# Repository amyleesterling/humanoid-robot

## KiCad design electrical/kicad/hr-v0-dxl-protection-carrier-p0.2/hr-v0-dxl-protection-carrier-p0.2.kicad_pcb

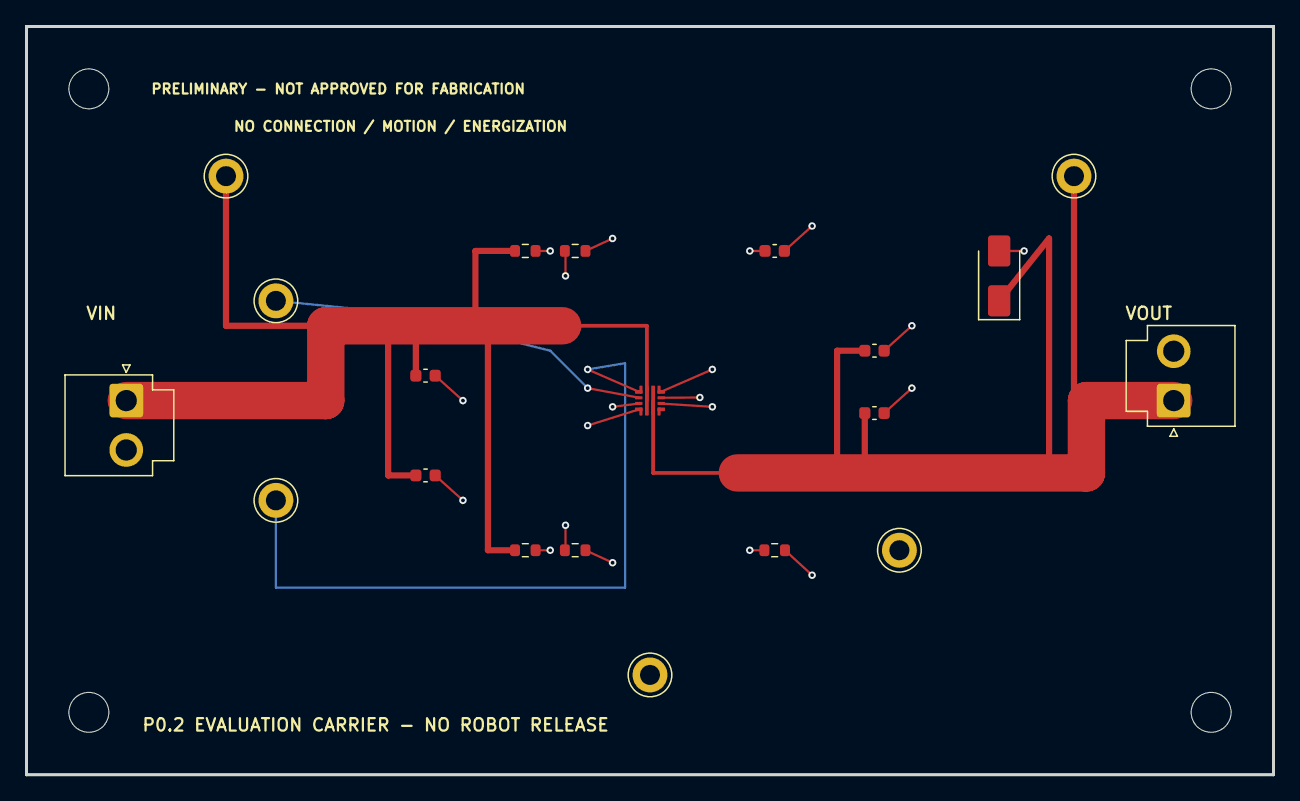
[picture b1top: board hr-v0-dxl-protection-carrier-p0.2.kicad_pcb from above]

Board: 4 copper layers, 100.0 x 60.0 mm, 24 parts (0 on the bottom side), 9 nets.

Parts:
CDV1: 2.2 nF C1608C0G1H222J080AA; C_0603_1608Metric
CINBULK1: 1 uF C1608X7R1V105K080AC; C_0603_1608Metric
CINHF1: 0.1 uF C1608X7R1H104K080AA; C_0603_1608Metric
COUTA1: 1 uF C1608X7R1V105K080AC; C_0603_1608Metric
COUTB1: 1 uF C1608X7R1V105K080AC; C_0603_1608Metric
DCLAMP1: B330A-13-F; D_SMA
JIN1: JST B2P-VH INPUT; JST_VH_B2P-VH_1x02_P3.96mm_Vertical
JOUT1: JST B2P-VH OUTPUT; JST_VH_B2P-VH_1x02_P3.96mm_Vertical
MH1, MH2, MH3, MH4: BOARD-ONLY M3; MOUNTING SELECTION REQUIRED; MountingHole_3.2mm_M3
RILM1: ASSEMBLY VARIANT: 1.65 k / 3.32 k; R_0603_1608Metric
ROVB1: 44.2 k RC0603FR-0744K2L; R_0603_1608Metric
ROVT1: 470 k RC0603FR-07470KL; R_0603_1608Metric
RUVB1: 49.9 k RC0603FR-0749K9L; R_0603_1608Metric
RUVT1: 365 k RC0603FR-07365KL; R_0603_1608Metric
TPFLT1: Keystone 5012 FLT; TestPoint_Keystone_5010-5014_Multipurpose
TPGND1: Keystone 5011 GND; TestPoint_Keystone_5010-5014_Multipurpose
TPILM1: Keystone 5012 ILM; TestPoint_Keystone_5010-5014_Multipurpose
TPOUT1: Keystone 5010 VOUT; TestPoint_Keystone_5010-5014_Multipurpose
TPSPLY1: Keystone 5012 SPLYGD; TestPoint_Keystone_5010-5014_Multipurpose
TPVIN1: Keystone 5010 VIN; TestPoint_Keystone_5010-5014_Multipurpose
U1: TPS259461LRPWR; TI_RPW0010A_HotRodQFN_2x2mm_P0.45mm_TI4225183A_P02

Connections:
ACT_0V_PE_BONDED: CDV1.2, CINBULK1.2, CINHF1.2, COUTA1.2, COUTB1.2, DCLAMP1.2, JIN1.2, JOUT1.2, RILM1.2, ROVB1.2, RUVB1.2, TPGND1.1, U1.8
BRANCH_FUSED_IN: CINBULK1.1, CINHF1.1, JIN1.1, ROVT1.1, RUVT1.1, TPVIN1.1, U1.5
BRANCH_LIMITED_OUT: COUTA1.1, COUTB1.1, DCLAMP1.1, JOUT1.1, TPOUT1.1, U1.6
DVDT_SET: CDV1.1, U1.7
FLT_DIAG: TPFLT1.1, U1.4
ILM_SET: RILM1.1, TPILM1.1, U1.9
OVLO_SET: ROVB1.1, ROVT1.2, U1.2
SPLYGD_DIAG: TPSPLY1.1, U1.3
UVLO_SET: RUVB1.1, RUVT1.2, U1.1

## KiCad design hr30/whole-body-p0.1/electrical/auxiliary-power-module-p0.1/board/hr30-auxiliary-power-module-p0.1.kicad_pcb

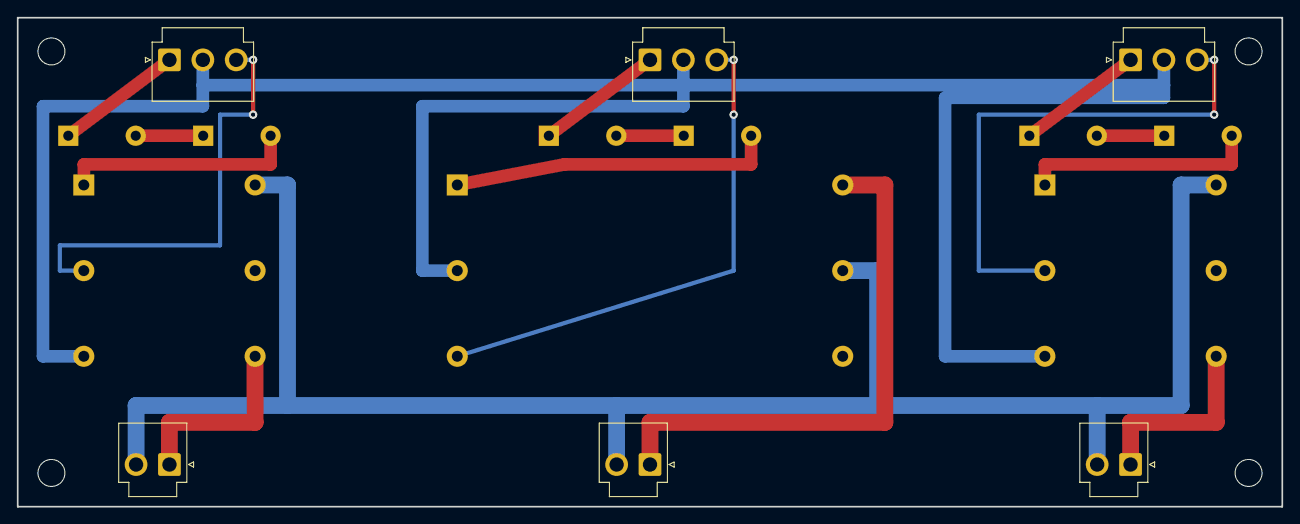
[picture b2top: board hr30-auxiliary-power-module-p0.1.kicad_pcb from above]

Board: 2 copper layers, 150.0 x 58.0 mm, 19 parts (0 on the bottom side), 17 nets.

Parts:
F1: COMPUTE input fuse - SELECTION REQUIRED; AUX_SELECTION_BLOCK
F2: HMI input fuse - SELECTION REQUIRED; AUX_SELECTION_BLOCK
F3: CONTROL input fuse - SELECTION REQUIRED; AUX_SELECTION_BLOCK
H1, H2, H3, H4: M3 BOARD MOUNT - STACK/FASTENER SELECTION REQUIRED; MountingHole_3.2mm_M3
JI1: COMPUTE 12 V input and active-low disable; JST_VH_B3P-VH-B_1x03_P3.96mm_Vertical
JI2: HMI 12 V input and active-low disable; JST_VH_B3P-VH-B_1x03_P3.96mm_Vertical
JI3: CONTROL 12 V input and active-low disable; JST_VH_B3P-VH-B_1x03_P3.96mm_Vertical
JO1: COMPUTE protected output; JST_VH_B2P-VH-B_1x02_P3.96mm_Vertical
JO2: HMI protected output; JST_VH_B2P-VH-B_1x02_P3.96mm_Vertical
JO3: CONTROL protected output; JST_VH_B2P-VH-B_1x02_P3.96mm_Vertical
RP1: COMPUTE reverse-polarity and inrush block - SELEC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; AUX_SELECTION_BLOCK
RP2: HMI reverse-polarity and inrush block - SELECTION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; AUX_SELECTION_BLOCK
RP3: CONTROL reverse-polarity and inrush block - SELEC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; AUX_SELECTION_BLOCK
U1: REC30E-2405SZ COMPUTE isolated converter; REC30E-Z
U2: TEN 40-1211E HMI isolated converter; TEN40E
U3: REC30E-2405SZ CONTROL isolated converter; REC30E-Z

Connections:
ACT_0V_CONTROLLED: JI1.2, JI2.2, JI3.2, U1.2, U2.2, U3.2
AUX_0V_STAR: JO1.2, JO2.2, JO3.2, U1.4, U2.5, U3.4
AUX_5V_SAFE: JO3.1, U3.6
COMPUTE_5V1: JO1.1, U1.6
COMPUTE_12V_FUSED: F1.2, RP1.1
COMPUTE_12V_PROTECTED: RP1.2, U1.1
COMPUTE_12V_RAW: F1.1, JI1.1
COMPUTE_DISABLE_N: JI1.3, U1.3
CONTROL_12V_FUSED: F3.2, RP3.1
CONTROL_12V_PROTECTED: RP3.2, U3.1
CONTROL_12V_RAW: F3.1, JI3.1
CONTROL_DISABLE_N: JI3.3, U3.3
HMI_5V0: JO2.1, U2.4
HMI_12V_FUSED: F2.2, RP2.1
HMI_12V_PROTECTED: RP2.2, U2.1
HMI_12V_RAW: F2.1, JI2.1
HMI_DISABLE_N: JI2.3, U2.3

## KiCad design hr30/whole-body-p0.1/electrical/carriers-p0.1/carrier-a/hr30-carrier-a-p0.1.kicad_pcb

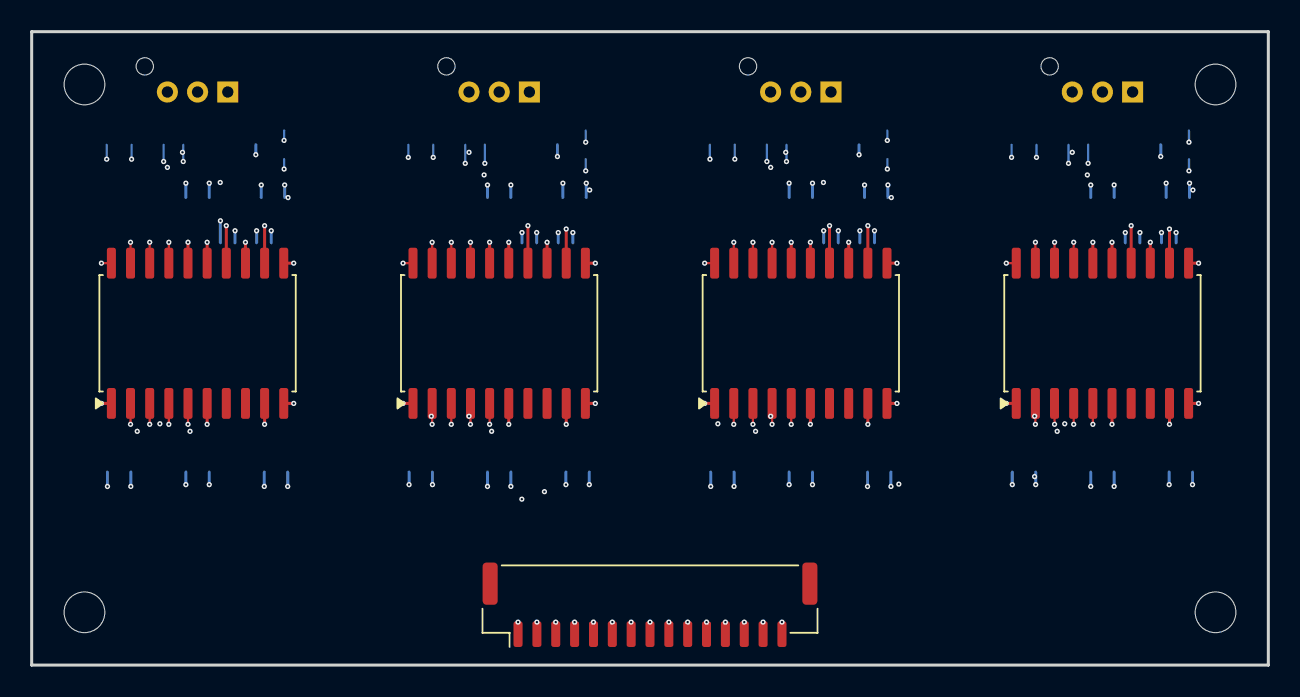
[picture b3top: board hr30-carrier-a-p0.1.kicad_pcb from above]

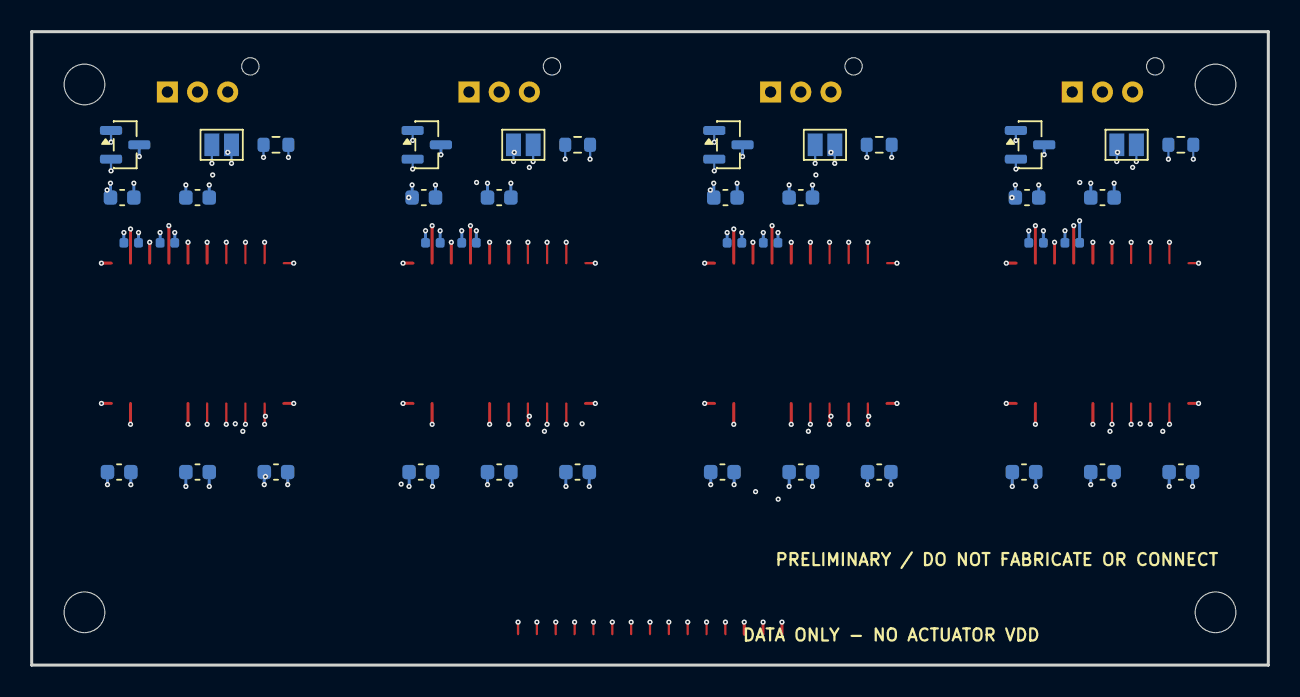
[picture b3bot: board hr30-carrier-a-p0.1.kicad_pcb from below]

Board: 6 copper layers, 82.0 x 42.0 mm, 53 parts (40 on the bottom side), 43 nets.

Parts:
C1A, C2A, C3A, C4A: 10nF 50V X7R; C_0603_1608Metric
C1B, C1D, C2B, C2D, C3B, C3D, C4B, C4D: 10uF 6.3V X5R; C_0603_1608Metric
C1C, C1E, C2C, C2E, C3C, C3E, C4C, C4E: 100nF 50V X7R; C_0603_1608Metric
D1RS, D2RS, D3RS, D4RS: SM712 RS-485 TVS; SOT-23
FB1N, FB2N, FB3N, FB4N: 330R@100MHz isolated return bead; L_0402_1005Metric
FB1P, FB2P, FB3P, FB4P: 330R@100MHz isolated supply bead; L_0402_1005Metric
J101: RS-LLEG data-only field; JST_PA_B03B-PASK-1
J102: RS-RLEG data-only field; JST_PA_B03B-PASK-1
J103: RS-LARM data-only field; JST_PA_B03B-PASK-1
J104: RS-RARM data-only field; JST_PA_B03B-PASK-1
JCA1: JST BM15B-GHS-TBT controller; JST_GH_BM15B-GHS-TBT_1x15-1MP_P1.25mm_Vertical
MHA1, MHA2, MHA3, MHA4: M2.5 BOARD-ONLY; TRAY STACK VALIDATION OPEN; MountingHole_2.7mm_M2.5
RT1, RT2, RT3, RT4: 120R 1% termination; R_0603_1608Metric
SJ1, SJ2, SJ3, SJ4: termination enable - OPEN; SolderJumper-2_P1.3mm_Open_Pad1.0x1.5mm
U101: ISOW1432DFMR RS-LLEG; SOIC-20W_7.5x12.8mm_P1.27mm
U102: ISOW1432DFMR RS-RLEG; SOIC-20W_7.5x12.8mm_P1.27mm
U103: ISOW1432DFMR RS-LARM; SOIC-20W_7.5x12.8mm_P1.27mm
U104: ISOW1432DFMR RS-RARM; SOIC-20W_7.5x12.8mm_P1.27mm

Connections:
CTRL_3V3: C1C.1, C2C.1, C3C.1, C4C.1, JCA1.3, U101.1, U102.1, U103.1, U104.1
CTRL_5V: C1A.1, C1B.1, C2A.1, C2B.1, C3A.1, C3B.1, C4A.1, C4B.1, JCA1.2, U101.9, U102.9, U103.9, U104.9
CTRL_GND: C1A.2, C1B.2, C1C.2, C2A.2, C2B.2, C2C.2, C3A.2, C3B.2, C3C.2, C4A.2, C4B.2, C4C.2, JCA1.1, U101.6, U101.10, U102.6, U102.10, U103.6, U103.10, U104.6, U104.10
RS-LARM_DN: D3RS.2, J103.3, SJ3.2, U103.18, U103.19
RS-LARM_DP: D3RS.1, J103.2, RT3.1, U103.17, U103.20
RS-LARM_GND2: C3D.2, FB3N.1, U103.11, U103.13
RS-LARM_RET: C3E.2, D3RS.3, FB3N.2, J103.1, U103.14, U103.15
RS-LARM_TERM: RT3.2, SJ3.1
RS-LARM_VISOIN: C3E.1, FB3P.2, U103.16
RS-LARM_VISOOUT: C3D.1, FB3P.1, U103.12
RS-LLEG_DN: D1RS.2, J101.3, SJ1.2, U101.18, U101.19
RS-LLEG_DP: D1RS.1, J101.2, RT1.1, U101.17, U101.20
RS-LLEG_GND2: C1D.2, FB1N.1, U101.11, U101.13
RS-LLEG_RET: C1E.2, D1RS.3, FB1N.2, J101.1, U101.14, U101.15
RS-LLEG_TERM: RT1.2, SJ1.1
RS-LLEG_VISOIN: C1E.1, FB1P.2, U101.16
RS-LLEG_VISOOUT: C1D.1, FB1P.1, U101.12
RS-RARM_DN: D4RS.2, J104.3, SJ4.2, U104.18, U104.19
RS-RARM_DP: D4RS.1, J104.2, RT4.1, U104.17, U104.20
RS-RARM_GND2: C4D.2, FB4N.1, U104.11, U104.13
RS-RARM_RET: C4E.2, D4RS.3, FB4N.2, J104.1, U104.14, U104.15
RS-RARM_TERM: RT4.2, SJ4.1
RS-RARM_VISOIN: C4E.1, FB4P.2, U104.16
RS-RARM_VISOOUT: C4D.1, FB4P.1, U104.12
RS-RLEG_DN: D2RS.2, J102.3, SJ2.2, U102.18, U102.19
RS-RLEG_DP: D2RS.1, J102.2, RT2.1, U102.17, U102.20
RS-RLEG_GND2: C2D.2, FB2N.1, U102.11, U102.13
RS-RLEG_RET: C2E.2, D2RS.3, FB2N.2, J102.1, U102.14, U102.15
RS-RLEG_TERM: RT2.2, SJ2.1
RS-RLEG_VISOIN: C2E.1, FB2P.2, U102.16
RS-RLEG_VISOOUT: C2D.1, FB2P.1, U102.12
UART_RS-LARM_DIR: JCA1.12, U103.3, U103.5
UART_RS-LARM_RX: JCA1.11, U103.4
UART_RS-LARM_TX: JCA1.10, U103.2
UART_RS-LLEG_DIR: JCA1.6, U101.3, U101.5
UART_RS-LLEG_RX: JCA1.5, U101.4
UART_RS-LLEG_TX: JCA1.4, U101.2
UART_RS-RARM_DIR: JCA1.15, U104.3, U104.5
UART_RS-RARM_RX: JCA1.14, U104.4
UART_RS-RARM_TX: JCA1.13, U104.2
UART_RS-RLEG_DIR: JCA1.9, U102.3, U102.5
UART_RS-RLEG_RX: JCA1.8, U102.4
UART_RS-RLEG_TX: JCA1.7, U102.2

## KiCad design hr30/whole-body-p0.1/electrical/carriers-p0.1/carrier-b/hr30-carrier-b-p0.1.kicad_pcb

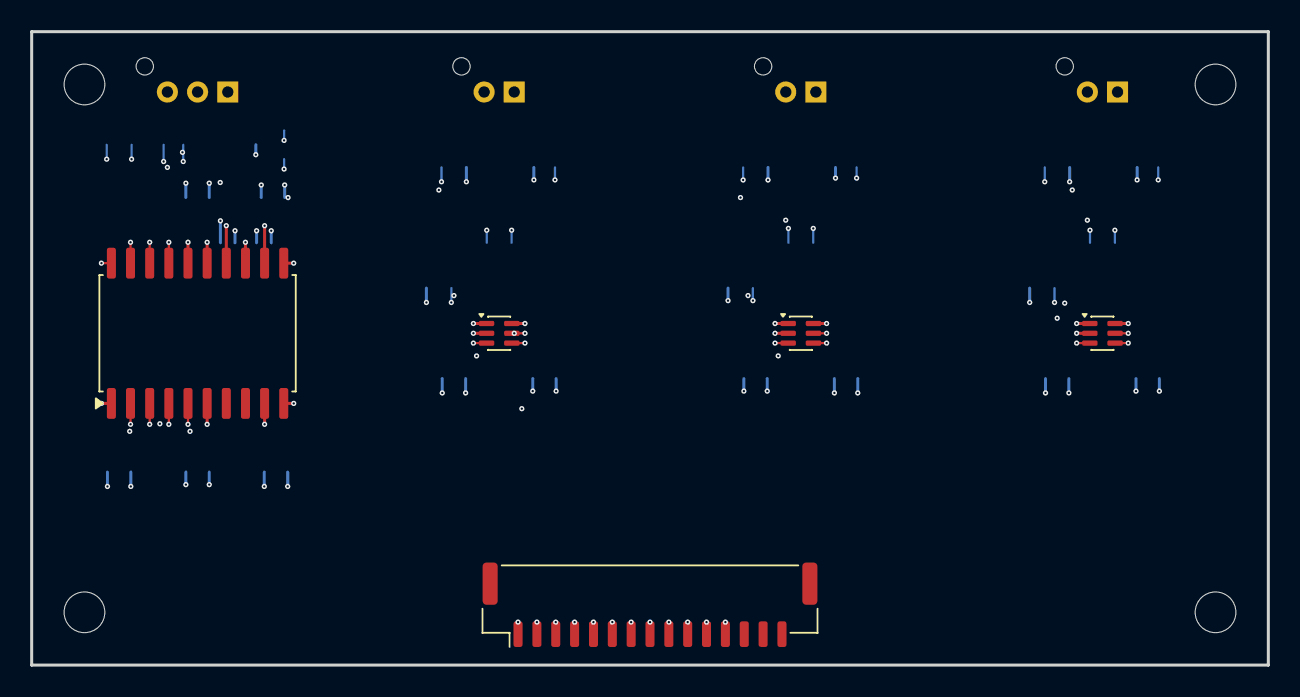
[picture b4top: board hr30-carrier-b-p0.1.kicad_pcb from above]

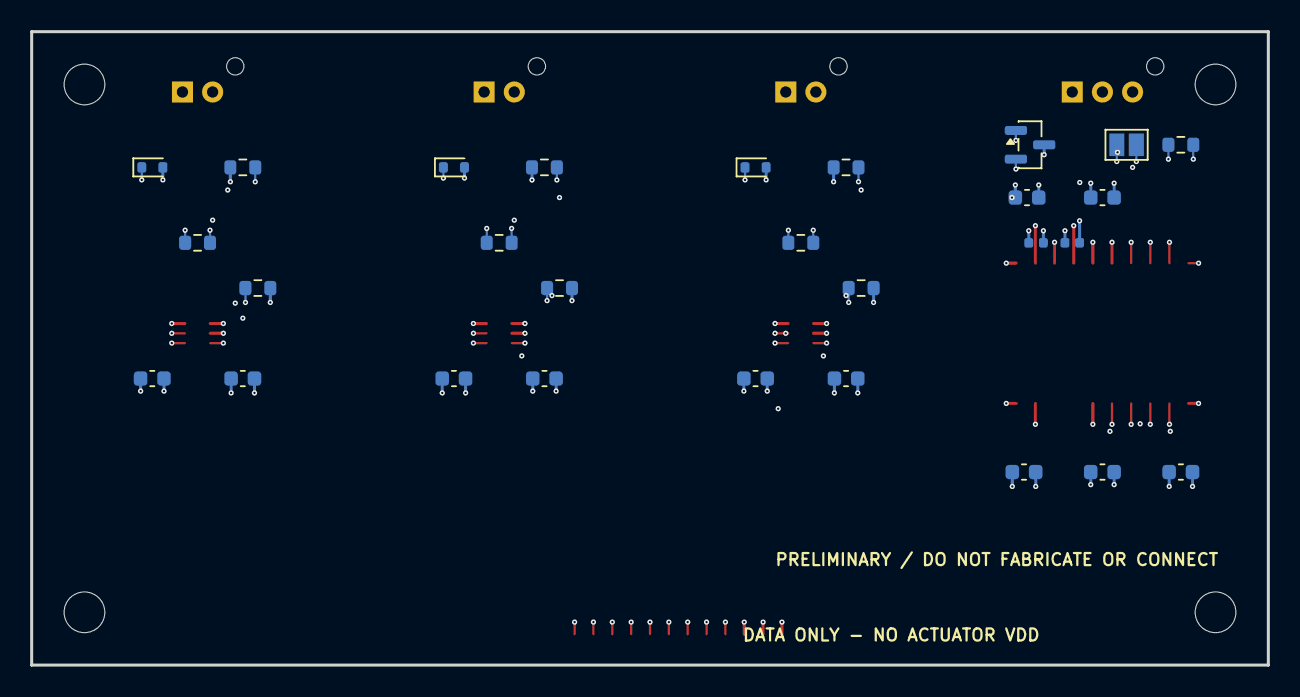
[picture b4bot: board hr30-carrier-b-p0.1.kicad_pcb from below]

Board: 6 copper layers, 82.0 x 42.0 mm, 41 parts (28 on the bottom side), 25 nets.

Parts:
C5A: 10nF 50V X7R; C_0603_1608Metric
C5B, C5D: 10uF 6.3V X5R; C_0603_1608Metric
C5C, C5E: 100nF 50V X7R; C_0603_1608Metric
C201A, C202A, C203A: 100nF 50V X7R VCCA; C_0603_1608Metric
C201B, C202B, C203B: 100nF 50V X7R VCCB; C_0603_1608Metric
D5RS: SM712 RS-485 TVS; SOT-23
D201, D202, D203: TPD1E10B06 TTL ESD; D_SOD-523
FB5N: 330R@100MHz isolated return bead; L_0402_1005Metric
FB5P: 330R@100MHz isolated supply bead; L_0402_1005Metric
J105: RS-WAIST data-only field; JST_PA_B03B-PASK-1
J201: TTL-LDIST data-only field; JST_PA_B02B-PASK-1
J202: TTL-RDIST data-only field; JST_PA_B02B-PASK-1
J203: TTL-HEAD data-only field; JST_PA_B02B-PASK-1
JCB1: JST BM15B-GHS-TBT controller; JST_GH_BM15B-GHS-TBT_1x15-1MP_P1.25mm_Vertical
MHB1, MHB2, MHB3, MHB4: M2.5 BOARD-ONLY; TRAY STACK VALIDATION OPEN; MountingHole_2.7mm_M2.5
R201D, R202D, R203D: 100k 1% DIR pulldown; R_0603_1608Metric
R201P, R202P, R203P: 10k idle pullup - DNP; R_0603_1608Metric
R201S, R202S, R203S: 33R 1% series; R_0603_1608Metric
RT5: 120R 1% termination; R_0603_1608Metric
SJ5: termination enable - OPEN; SolderJumper-2_P1.3mm_Open_Pad1.0x1.5mm
U105: ISOW1432DFMR RS-WAIST; SOIC-20W_7.5x12.8mm_P1.27mm
U201: SN74LVC1T45DCKR TTL-LDIST; SOT-363_SC-70-6
U202: SN74LVC1T45DCKR TTL-RDIST; SOT-363_SC-70-6
U203: SN74LVC1T45DCKR TTL-HEAD; SOT-363_SC-70-6

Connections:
CTRL_3V3: C5C.1, C201A.1, C202A.1, C203A.1, JCB1.3, U105.1, U201.1, U202.1, U203.1
CTRL_5V: C5A.1, C5B.1, C201B.1, C202B.1, C203B.1, JCB1.2, R201P.1, R202P.1, R203P.1, U105.9, U201.6, U202.6, U203.6
CTRL_GND: C5A.2, C5B.2, C5C.2, C201A.2, C201B.2, C202A.2, C202B.2, C203A.2, C203B.2, D201.2, D202.2, D203.2, J201.1, J202.1, J203.1, JCB1.1, R201D.2, R202D.2, R203D.2, U105.6, U105.10, U201.2, U202.2, U203.2
RS-WAIST_DN: D5RS.2, J105.3, SJ5.2, U105.18, U105.19
RS-WAIST_DP: D5RS.1, J105.2, RT5.1, U105.17, U105.20
RS-WAIST_GND2: C5D.2, FB5N.1, U105.11, U105.13
RS-WAIST_RET: C5E.2, D5RS.3, FB5N.2, J105.1, U105.14, U105.15
RS-WAIST_TERM: RT5.2, SJ5.1
RS-WAIST_VISOIN: C5E.1, FB5P.2, U105.16
RS-WAIST_VISOOUT: C5D.1, FB5P.1, U105.12
TTL-HEAD_DATA: D203.1, J203.2, R203P.2, R203S.2
TTL-HEAD_DATA_PRE: R203S.1, U203.4
TTL-LDIST_DATA: D201.1, J201.2, R201P.2, R201S.2
TTL-LDIST_DATA_PRE: R201S.1, U201.4
TTL-RDIST_DATA: D202.1, J202.2, R202P.2, R202S.2
TTL-RDIST_DATA_PRE: R202S.1, U202.4
UART_RS-WAIST_DIR: JCB1.6, U105.3, U105.5
UART_RS-WAIST_RX: JCB1.5, U105.4
UART_RS-WAIST_TX: JCB1.4, U105.2
UART_TTL-HEAD_DIR: JCB1.12, R203D.1, U203.5
UART_TTL-HEAD_TX: JCB1.11, U203.3
UART_TTL-LDIST_DIR: JCB1.8, R201D.1, U201.5
UART_TTL-LDIST_TX: JCB1.7, U201.3
UART_TTL-RDIST_DIR: JCB1.10, R202D.1, U202.5
UART_TTL-RDIST_TX: JCB1.9, U202.3

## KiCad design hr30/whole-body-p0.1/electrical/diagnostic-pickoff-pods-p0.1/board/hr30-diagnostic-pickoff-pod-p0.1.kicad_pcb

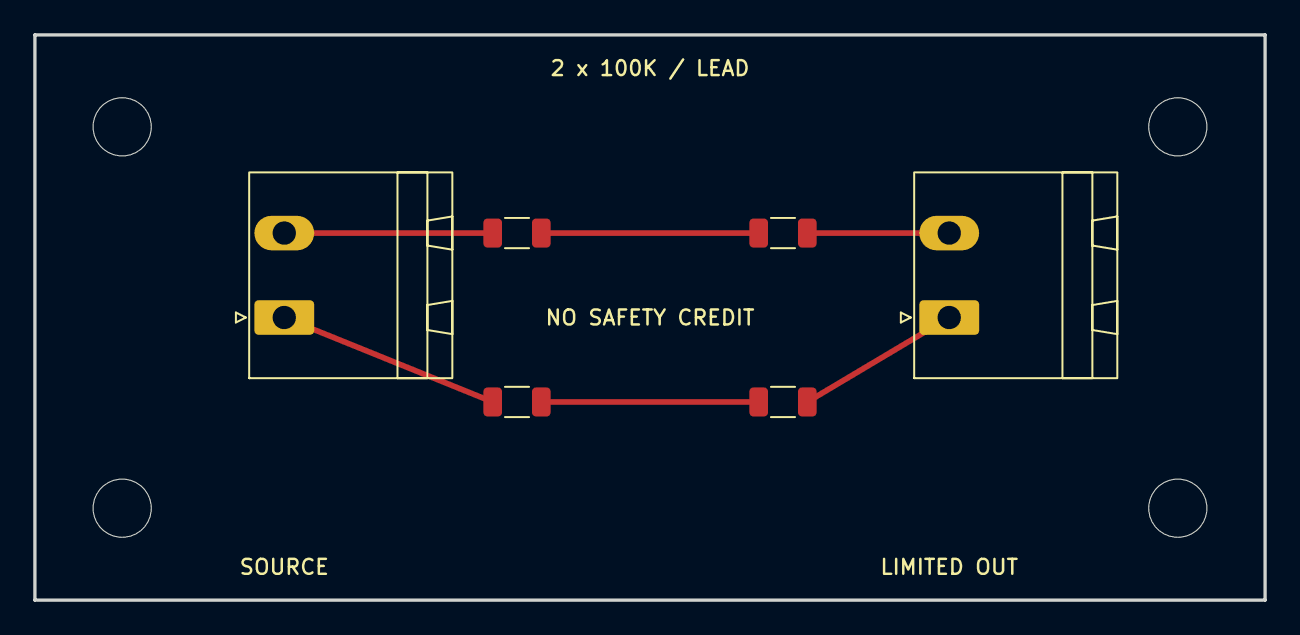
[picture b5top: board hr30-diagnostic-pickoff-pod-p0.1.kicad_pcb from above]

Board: 2 copper layers, 74.0 x 34.0 mm, 10 parts (0 on the bottom side), 6 nets.

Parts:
H1, H2, H3, H4: HAMMOND 1551KFL STANDOFF CANDIDATE; MountingHole_3.5mm
JIN: 1757242; PhoenixContact_MSTBA_2,5_2-G-5,08_1x02_P5.08mm_Horizontal
JOUT: 1757242; PhoenixContact_MSTBA_2,5_2-G-5,08_1x02_P5.08mm_Horizontal
RHA: TNPW1206100KBEEA; R_1206_3216Metric
RHB: TNPW1206100KBEEA; R_1206_3216Metric
RLA: TNPW1206100KBEEA; R_1206_3216Metric
RLB: TNPW1206100KBEEA; R_1206_3216Metric

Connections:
HI_MID: RHA.2, RHB.1
LO_MID: RLA.2, RLB.1
OUT_HI: JOUT.1, RHB.2
OUT_LO: JOUT.2, RLB.2
SRC_HI: JIN.1, RHA.1
SRC_LO: JIN.2, RLA.1

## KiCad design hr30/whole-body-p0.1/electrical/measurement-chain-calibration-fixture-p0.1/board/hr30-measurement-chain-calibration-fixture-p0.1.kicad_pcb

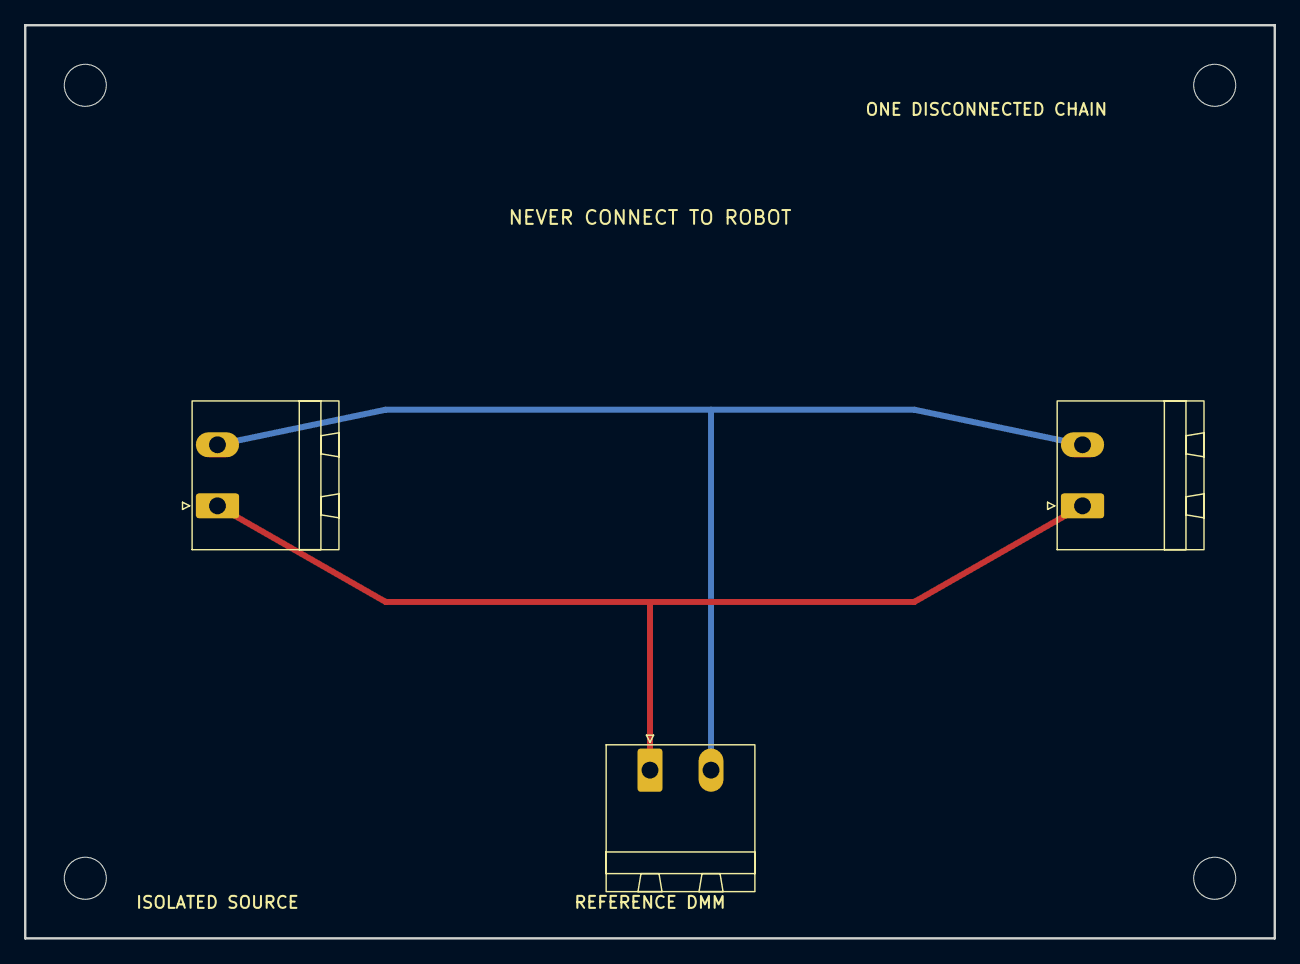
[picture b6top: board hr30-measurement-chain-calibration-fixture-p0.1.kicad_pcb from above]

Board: 2 copper layers, 104.0 x 76.0 mm, 7 parts (0 on the bottom side), 2 nets.

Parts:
H1, H2, H3, H4: ENCLOSURE STANDOFF FAI REQUIRED; MountingHole_3.5mm
JDMM: 1757242; PhoenixContact_MSTBA_2,5_2-G-5,08_1x02_P5.08mm_Horizontal
JDUT: 1757242; PhoenixContact_MSTBA_2,5_2-G-5,08_1x02_P5.08mm_Horizontal
JPS: 1757242; PhoenixContact_MSTBA_2,5_2-G-5,08_1x02_P5.08mm_Horizontal

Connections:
CAL_HI: JDMM.1, JDUT.1, JPS.1
CAL_LO: JDMM.2, JDUT.2, JPS.2

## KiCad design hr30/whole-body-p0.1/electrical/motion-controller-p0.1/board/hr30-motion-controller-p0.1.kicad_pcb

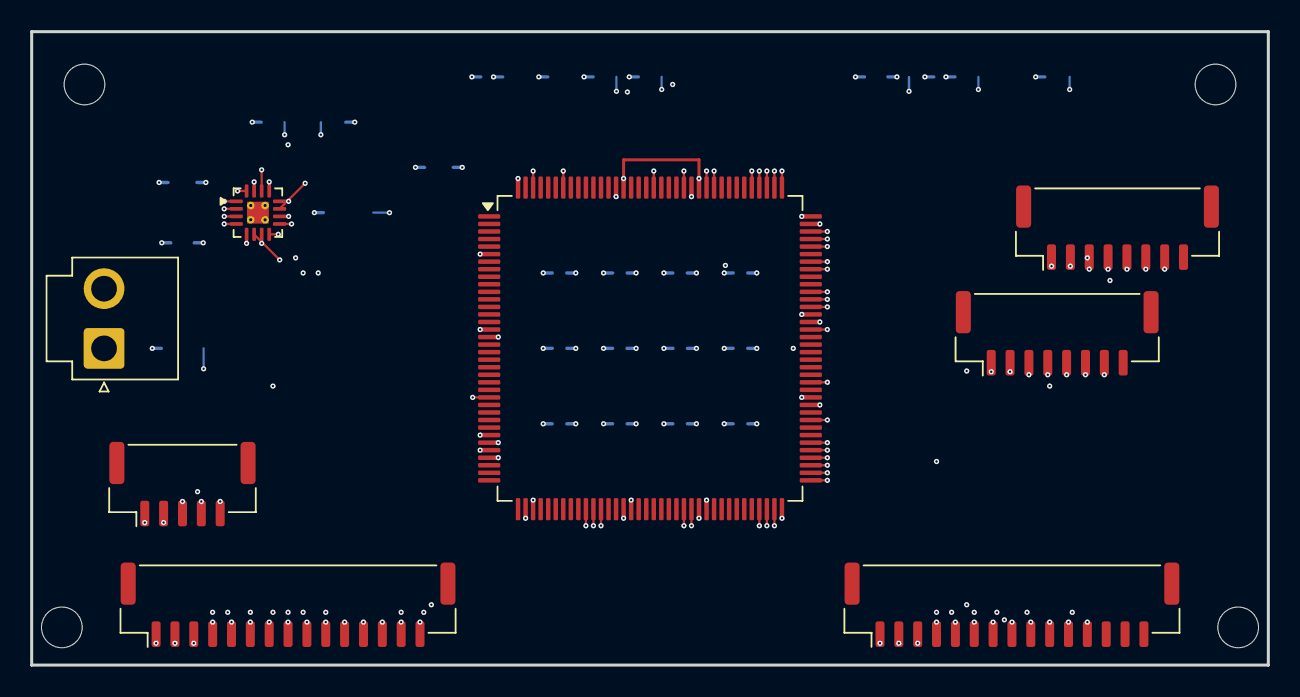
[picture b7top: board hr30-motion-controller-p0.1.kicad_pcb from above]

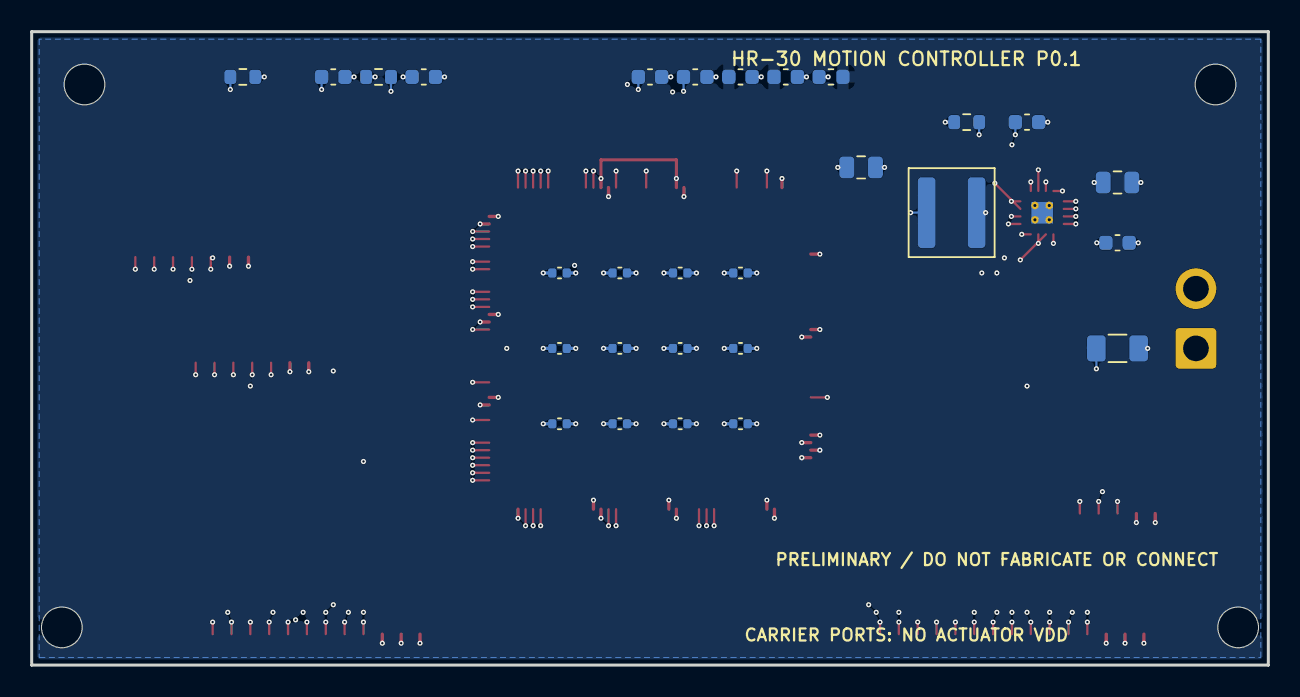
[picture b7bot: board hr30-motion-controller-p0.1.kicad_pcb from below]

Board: 6 copper layers, 82.0 x 42.0 mm, 40 parts (28 on the bottom side), 45 nets.

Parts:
C1, C2, C3, C4, C5, C6, C7, C8, C9, C10, C11, C12: 100 nF MCU supply bypass; C_0402_1005Metric
CANA1: 1 uF analog bypass; C_0603_1608Metric
CANA2: 100 nF analog bypass; C_0603_1608Metric
CBULK1: 4.7 uF MCU bulk; C_0603_1608Metric
CIN1: 10 uF 10 V X7R input; C_0805_2012Metric
CIN2: 100 nF 50 V X7R AVIN; C_0603_1608Metric
CNRST: 100 nF NRST filter; C_0603_1608Metric
COUT1: 22 uF 6.3 V X5R output; C_0805_2012Metric
CSS1: 3.3 nF soft-start; C_0603_1608Metric
CVC1: 2.2 uF VCAP1; C_0603_1608Metric
CVC2: 2.2 uF VCAP2; C_0603_1608Metric
F1: resettable input protection - selection required; Fuse_1206_3216Metric
FB1: analog-rail ferrite; L_0603_1608Metric
J1: Protected auxiliary 5 V input; JST_VH_B2P-VH-B_1x02_P3.96mm_Vertical
JACT1: structured action SPI boundary; JST_GH_BM08B-GHS-TBT_1x08-1MP_P1.25mm_Vertical
JCA1: Carrier A logic-only interface; JST_GH_BM15B-GHS-TBT_1x15-1MP_P1.25mm_Vertical
JCB1: Carrier B logic-only interface; JST_GH_BM15B-GHS-TBT_1x15-1MP_P1.25mm_Vertical
JDBG1: SWD programming/debug; JST_GH_BM05B-GHS-TBT_1x05-1MP_P1.25mm_Vertical
JIO1: deterministic status / inhibit I/O; JST_GH_BM08B-GHS-TBT_1x08-1MP_P1.25mm_Vertical
L1: 2.2 uH power inductor; L_Coilcraft_XAL5030-XXX
MHM1, MHM2, MHM3, MHM4: M2.5 BOARD-ONLY; TRAY STACK VALIDATION OPEN; MountingHole_2.7mm_M2.5
RBOOT: 100 k BOOT0 pull-down; R_0603_1608Metric
RNRST: 10 k NRST pull-up; R_0603_1608Metric
RPG1: 100 k power-good pull-up; R_0603_1608Metric
U1: STM32H743ZIT6 deterministic motion controller; LQFP-144_20x20mm_P0.5mm
U2: TPS62132 3.3 V / 3 A buck; VQFN-16-1EP_3x3mm_P0.5mm_EP1.45x1.45mm_ThermalVias

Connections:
ACTION_READY: JACT1.7, U1.126
ACTION_SPI_CS: JACT1.3, U1.73
ACTION_SPI_MISO: JACT1.5, U1.75
ACTION_SPI_MOSI: JACT1.6, U1.76
ACTION_SPI_SCK: JACT1.4, U1.74
AUX_5V_SAFE: F1.1, J1.2
BUCK_PG: RPG1.2, U2.4
BUCK_SS: CSS1.1, U2.9
BUCK_SW: L1.1, U2.1, U2.2, U2.3
CTRL_3V3: C1.1, C2.1, C3.1, C4.1, C5.1, C6.1, C7.1, C8.1, C9.1, C10.1, C11.1, C12.1, CBULK1.1, COUT1.1, FB1.1, JACT1.2, JCA1.3, JCB1.3, JDBG1.2, JIO1.2, L1.2, RNRST.1, RPG1.1, U1.6, U1.17, U1.30, U1.39, U1.52, U1.62, U1.72, U1.84, U1.95, U1.108, U1.121, U1.131, U1.144, U2.14
CTRL_3V3_ANALOG: CANA1.1, CANA2.1, FB1.2, U1.32, U1.33
CTRL_5V: CIN1.1, CIN2.1, F1.2, JCA1.2, JCB1.2, U2.10, U2.11, U2.12, U2.13
CTRL_GND: C1.2, C2.2, C3.2, C4.2, C5.2, C6.2, C7.2, C8.2, C9.2, C10.2, C11.2, C12.2, CANA1.2, CANA2.2, CBULK1.2, CIN1.2, CIN2.2, CNRST.2, COUT1.2, CSS1.2, CVC1.2, CVC2.2, J1.1, JACT1.1, JCA1.1, JCB1.1, JDBG1.1, JIO1.1, RBOOT.2, U1.16, U1.31, U1.38, U1.51, U1.61, U1.83, U1.94, U1.107, U1.120, U1.130, U2.5, U2.6, U2.7, U2.8, U2.15, U2.16, U2.17
MCU_BOOT0: RBOOT.1, U1.138
MCU_NRST: CNRST.1, JDBG1.5, RNRST.2, U1.25
MOTION_FAULT_DIAGNOSTIC: JIO1.7, U1.70
MOTION_WD_HEARTBEAT: JIO1.5, U1.48
PRECHARGE_REQUEST: JIO1.6, U1.69
PRECHARGE_STATUS: JIO1.4, U1.47
SAFETY_PERMIT_HARDWIRED: JIO1.3, U1.46
SWCLK: JDBG1.4, U1.109
SWDIO: JDBG1.3, U1.105
UART_RS-LARM_DIR: JCA1.12, U1.81
UART_RS-LARM_RX: JCA1.11, U1.78
UART_RS-LARM_TX: JCA1.10, U1.77
UART_RS-LLEG_DIR: JCA1.6, U1.104
UART_RS-LLEG_RX: JCA1.5, U1.102
UART_RS-LLEG_TX: JCA1.4, U1.101
UART_RS-RARM_DIR: JCA1.15, U1.93
UART_RS-RARM_RX: JCA1.14, U1.97
UART_RS-RARM_TX: JCA1.13, U1.96
UART_RS-RLEG_DIR: JCA1.9, U1.118
UART_RS-RLEG_RX: JCA1.8, U1.122
UART_RS-RLEG_TX: JCA1.7, U1.119
UART_RS-WAIST_DIR: JCB1.6, U1.110
UART_RS-WAIST_RX: JCB1.5, U1.112
UART_RS-WAIST_TX: JCB1.4, U1.111
UART_TTL-HEAD_DIR: JCB1.12, U1.86
UART_TTL-HEAD_TX: JCB1.11, U1.142
UART_TTL-LDIST_DIR: JCB1.8, U1.98
UART_TTL-LDIST_TX: JCB1.7, U1.113
UART_TTL-RDIST_DIR: JCB1.10, U1.60
UART_TTL-RDIST_TX: JCB1.9, U1.59
VCAP1: CVC1.1, U1.71
VCAP2: CVC2.1, U1.106

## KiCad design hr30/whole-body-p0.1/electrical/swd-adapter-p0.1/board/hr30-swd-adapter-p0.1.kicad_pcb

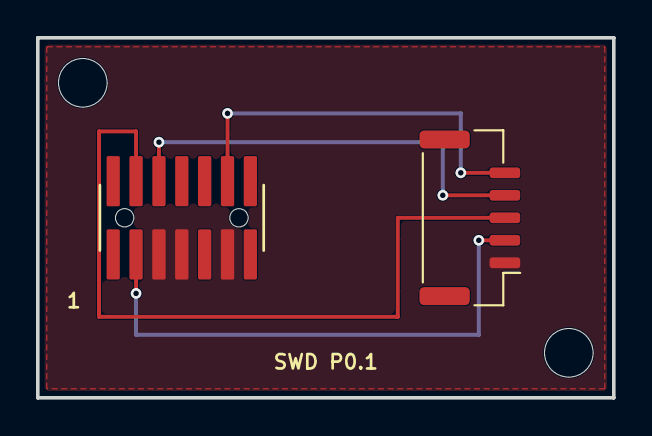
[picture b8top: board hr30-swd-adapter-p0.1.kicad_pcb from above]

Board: 2 copper layers, 32.0 x 20.0 mm, 4 parts (0 on the bottom side), 5 nets.

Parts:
H1, H2: M2.5 FIXTURE HOLE - MECHANICAL VALIDATION OPEN; MountingHole_2.7mm_M2.5
J1: FTSH-107-01-L-DV-K-A
J2: BM05B-GHS-TBT; JST_GH_BM05B-GHS-TBT_1x05-1MP_P1.25mm_Vertical

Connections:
CTRL_3V3: J1.3, J2.2
CTRL_GND: J1.5, J1.7, J1.11, J2.1
MCU_NRST: J1.12, J2.5
SWCLK: J1.6, J2.4
SWDIO: J1.4, J2.3
